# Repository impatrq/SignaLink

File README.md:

<div align="center">

</div>

<div align="center">

# Tus gestos hablan, SignaLink traduce

</div>

<table align="center">
<tr>
<td align="center">

</td>
<td align="center">

</td>
</tr>
</table>

## 📽️ Video de Presentación:

<a href="https://www.youtube.com/watch?v=zcVjxcC5Wm8&t=133s">Video de Presentación</a>

## 🔗 Acceso a página web:

<a href="https://signalink2025.com">Web Page</a>

## 🗓️ Objetivo de Proyecto:

SignaLink tiene como objetivo principal traducir la lengua de señas para lograr la inclusión de personas sordas en el ámbito escolar.

## 🌎 Visión a futuro

Otro objetivo propuesto a largo plazo es seguir difundiendo esta idea en futuras generaciones para poder proveerles un mejor manejo en la vida cotidiana a este tipo de personas, permitiendole agilizar su vida social o simplemente la comunicación sin barerras con otras personas.

## 💭 ¿De dónde surgió la idea?

Esta idea surgió en una conversación con la bibliotecaria de nuestra escuela que nos dio a conocer cuan reservadas son estas personas en la sociedad y cuantos desafios deben afrontar a diario. A traves de todo esto planteamos posibles soluciones para facilitarle sus vidas inicialmente en las escuelas y asi empezo toda esta aventura.

## 🖐 Descripción del proyecto:

Nuestro proyecto esta principalmente equipado con sensores flex, giroscopos y acelerómetros que detectan los movimientos de los dedos.

Estos datos que arrojan los sensores son capturados por un ESP32 C3 Super Mini ubicado en la muñeca y enviados a un Computer module 4 (CM4) a traves de un sistema de mensajeria (MQTT) ubicado en el pecho/cintura. Esta CM4 integra una Inteligencia Artificial (IA) que se encarga de procesar estos datos recibidos para descubrir que gesto se intentó hacer. Una vez realizado este proceso se convertira mediante PIPER-TTS a formato audio reproducible por un parlante, permitiendo así que las personas que se comunican mediante la lengua de señas puedan expresar su mensaje de forma audible para que cualquier receptor lo comprenda.

En paralelo, un micrófono direccional se encargará de captar la voz de la persona que quiera comunicarse, esas palabras serán procesadas por la CM4 utilizando un modelo de reconocimiento de voz (Vosk -> Offline) y en forma de texto se mostrará finalmente a través de un LCD OLED (SSD1306)

<div align="center">

</div>

## 🛠️ Componentes a utilizar:

| Componentes                     | Links                                                                                                                                                                                                                                                                                                                                                                                                                                                                                                                                                                                                                                                                                                                                                                                            |
| ------------------------------- | ------------------------------------------------------------------------------------------------------------------------------------------------------------------------------------------------------------------------------------------------------------------------------------------------------------------------------------------------------------------------------------------------------------------------------------------------------------------------------------------------------------------------------------------------------------------------------------------------------------------------------------------------------------------------------------------------------------------------------------------------------------------------------------------------ |
| Raspberry Pi Compute Module 4   | [Raspberry Pi Compute Module 4 - ELEMON](https://www.elemon.com.ar/products/detail/code/AR681RA642)                                                                                                                                                                                                                                                                                                                                                                                                                                                                                                                                                                                                                                                                                              |
| ESP32-C3 Super Mini             | [ESP32-C3 Super Mini - Mercado Libre](https://articulo.mercadolibre.com.ar/MLA-1933180704-placa-desarrollo-esp32-c3-super-mini-wifi-bluetooth-sgk-_JM#polycard_client=search-nordic&position=18&search_layout=grid&type=item&tracking_id=a6179d80-9c2f-448f-931d-3f6b0744610e&wid=MLA1933180704&sid=search)                                                                                                                                                                                                                                                                                                                                                                                                                                                                                      |
| Sensores Flex                   | [Sensores Flex - Mercado Libre](https://articulo.mercadolibre.com.ar/MLA-621168012-flex-sensor-45-o-degrees-10-30-kohms-sensor-reflectivo-_JM#polycard_client=search-nordic&position=22&search_layout=stack&type=item&tracking_id=d09a116e-7fa9-4e61-b811-829b67d77fb1&wid=MLA621168012&sid=search)                                                                                                                                                                                                                                                                                                                                                                                                                                                                                              |
| Parlante                        | [ Mini Parlante- Mercado Libre](https://articulo.mercadolibre.com.ar/MLA-926965993-mini-parlante-mylar-50mm-8-ohms-05w-audio-arduino-nubbeo-_JM#polycard_client=search-nordic&position=8&search_layout=stack&type=item&tracking_id=5afdc171-789b-4858-9908-6e8644b818c2&wid=MLA926965993&sid=search)                                                                                                                                                                                                                                                                                                                                                                                                                                                                                             |
| Modulo Amplificador             | [ PAM8403 - Mercado Libre](https://www.mercadolibre.com.ar/mini-amplificador-digital-pam8403-audio-estereo-3w-nubbeo/up/MLAU237136317?pdp_filters=item_id:MLA872767061&matt_tool=93069454&matt_internal_campaign_id=345755545&matt_word=&matt_source=google&matt_campaign_id=22943760643&matt_ad_group_id=187007705242&matt_match_type=&matt_network=g&matt_device=c&matt_creative=774178775740&matt_keyword=&matt_ad_position=&matt_ad_type=pla&matt_merchant_id=5381779497&matt_product_id=MLA872767061&matt_product_partition_id=2424609165763&matt_target_id=pla-2424609165763&cq_src=google_ads&cq_cmp=22943760643&cq_net=g&cq_plt=gp&cq_med=pla&gad_source=1&gad_campaignid=22943760643&gclid=CjwKCAjwx-zHBhBhEiwA7Kjq67psJOORAgfFyvkqrNDuf2QOjtHhOilyAz1d6FZmyiqMh8wAA7Ma8xoCBCEQAvD_BwE) |
| Micrófono                       | [ Corbatero Carello C11 - Mercado Libre](https://www.mercadolibre.com.ar/microfono-inalambrico-corbatero-lavalier-carrello-c11-adaptador-usb-c-a-lightning-estuche-de-carga-antena-usb-c-1x-microfono-color-negro/p/MLA44118282)                                                                                                                                                                                                                                                                                                                                                                                                                                                                                                                                                                 |
| Baterias                        | [ Lipo 3.7V - Mercado Libre](https://articulo.mercadolibre.com.ar/MLA-823943306-bateria-litio-polimero-lipo-37v-1200mah-drones-helicopteros-_JM#polycard_client=search-nordic&position=11&search_layout=stack&type=item&tracking_id=00997a8f-a302-41cd-929e-7f9b96588b73&wid=MLA823943306&sid=search)                                                                                                                                                                                                                                                                                                                                                                                                                                                                                            |
| Sensor Giroscopo y Acelerometro | [MPU6050 - Mercado Libre](https://articulo.mercadolibre.com.ar/MLA-1464073846-acelerometro-giroscopo-mpu6050-6-ejes-gy-521-pic-arduino-_JM#polycard_client=search-nordic&position=4&search_layout=grid&type=item&tracking_id=1592b6fb-67c2-4128-a466-704776d0e915&wid=MLA1464073846&sid=search)                                                                                                                                                                                                                                                                                                                                                                                                                                                                                                  |
| Step Up 5V                      | [ MT3608 - Mercado Libre](https://articulo.mercadolibre.com.ar/MLA-1410408453-5-fuente-mt3608-step-up-buck-boost-elevador-dc-dc-28v-2a-_JM#polycard_client=search-nordic&backend_model=search-backend&position=20&search_layout=stack&type=item&tracking_id=d4915a5c-d355-42a4-b246-3798a3844913&wid=MLA1410408453&sid=search)                                                                                                                                                                                                                                                                                                                                                                                                                                                                   |
| LCD OLED                        | [LCD SSD1306 - Mercado Libre](https://articulo.mercadolibre.com.ar/MLA-1899526208-pantalla-display-oled-091-pulgadas-128x32-i2c-ssd1306-_JM)                                                                                                                                                                                                                                                                                                                                                                                                                                                                                                                                                                                                                                                     |

## 💻 Instalación y Uso

1. Clonar el repositorio:
   ```bash
   git clone https://github.com/impatrq/SignaLink
   ```
2. Entrar a la carpeta rpizero2W.
   ```bash
   cd SignaLink/rpizero2W
   ```
3. Darle permisos de ejecucion al script de instalación.
   ```bash
   chmod +x install.sh
   ```
4. Ejecutar el Script.
   ```bash
   ./install.sh
   ```
5. Comenzar su uso.

## 🧑🏽‍💻 Integrantes

| Integrantes           | Responsabilidades                     | Tareas Secundarias                 |
| --------------------- | ------------------------------------- | ---------------------------------- |
| Albornoz Thiago       | Gestión de Redes Sociales y Marketing | Desarrollo de Software             |
| Erbino Sebastián      | Diseño del Prototipo                  | Integración de hardware            |
| Franco Valentin       | Armado de Hardware                    | Instalación y conexión de hardware |
| Lesme Franco          | Armado de software                    | Diseño del prototipo               |
| Poggi Lorenzo         | Registro de Seguimiento               | Programación del sistema           |
| Sarniguette Valentino | Prueba electronica                    | Armado de circuitos                |

## 🤝 Colaboración:

Este es el comienzo de un prototipo realizado a base de nuestros conocimientos, si le gustaria formar parte de SignaLink, nos ayudaría su colaboración en:

- Perfeccionar el código.
- Mejorar la infraestructura tecnológica.
- Creación de manuales y realización de pruebas.
- Apoyo financiero para la investigación y el desarrollo.

## 📱 Contactanos:

## 📱 Contactos personales

| Integrante                | Gmail                                                                                                                                                                          | LinkedIn                                                                                                                                                                                                                                            |
| ------------------------- | ------------------------------------------------------------------------------------------------------------------------------------------------------------------------------ | --------------------------------------------------------------------------------------------------------------------------------------------------------------------------------------------------------------------------------------------------- |
| **Albornoz Thiago**       |  |                                                                         |
| **Erbino Sebastian**      |              |                                                          |
| **Franco Valentin**       |     |  |
| **Lesme Franco**          |       |                                                                                 |
| **Poggi Lorenzo**         |     |    |
| **Sarniguette Valentino** |   |                                                                          |

---

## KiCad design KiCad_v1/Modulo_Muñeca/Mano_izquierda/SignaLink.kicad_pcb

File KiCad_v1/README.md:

# Carpeta de Trabajo - Diseño de Placas 

Utilizamos **KiCad** para el diseño de circuitos impresos (PCB). Llevamos con esta aplicacion la creacion de dos PCBs:

## Módulo Muñeca

El diseño de la placa está optimizado en un formato compacto de 30 mm por 50 mm, lo que permite reducir al máximo su tamaño sin afectar el rendimiento. Su objetivo principal es garantizar un sensado preciso de los gestos de la mano, combinando comodidad de uso con eficiencia en la interpretación de movimientos. 

El módulo integra un ESP32-C3 Super Mini como microcontrolador central, acompañado por el chip MPU6050 para la detección de aceleración y giro, una pantalla OLED SSD1306 para la visualización de información en tiempo real, sensores flexibles que registran la flexión de los dedos y un módulo de carga USB que facilita la autonomía energética y la recarga de Batería Lipo. Gracias a esta integración, el sistema se presenta como una solución ligera, compacta y confiable para la captura e interpretación de gestos manuales.

<h3>Mano Izquierda</h3>

- Diseño 3D:
<div align="center">

</div>

- Esquemático
<div align="center">

</div>

- Diseño de placa sin plano de masa
<div align="center">

</div>

- Diseño de placa con plano de masa:
<div align="center">

</div>

<h3>Mano Derecha</h3>

- Diseño 3D:
<div align="center">

</div>

- Esquemático
<div align="center">

</div>

- Diseño de placa sin plano de masa
<div align="center">

</div>

- Diseño de placa con plano de masa:
<div align="center">

</div>

## Modulo Pecho: 

El módulo del pecho constituye el núcleo de procesamiento de SignaLink. En su diseño se integra una Raspberry Pi Compute Module 4 (RCM4), que actúa como el procesador principal encargado de coordinar y analizar la información proveniente de los demás periféricos. Esta capacidad de cómputo permite realizar el filtrado de datos en tiempo real y gestionar la comunicación con el resto del sistema a través del protocolo MQTT, asegurando una transmisión eficiente y confiable.

Además de la RCM4, la placa incorpora un DAC con amplificador PAM junto con los conectores para parlante, lo que posibilita la conversión de gestos a audio de manera clara y directa. Gracias a esta integración, el sistema no solo traduce los movimientos capturados en datos procesables, sino que también ofrece la salida de voz que convierte las señas en un medio de comunicación audible.

De esta forma, el módulo del pecho se consolida como el cerebro y la voz de SignaLink, combinando procesamiento, conectividad y salida de audio en una sola unidad compacta y eficiente.

- Diseño 3D:
<div align="center">

</div>

- Diseño 3D:
<div align="center">

</div>

- Esquemático
<div align="center">

</div>

- Diseño de placa sin plano de masa
<div align="center">

</div>

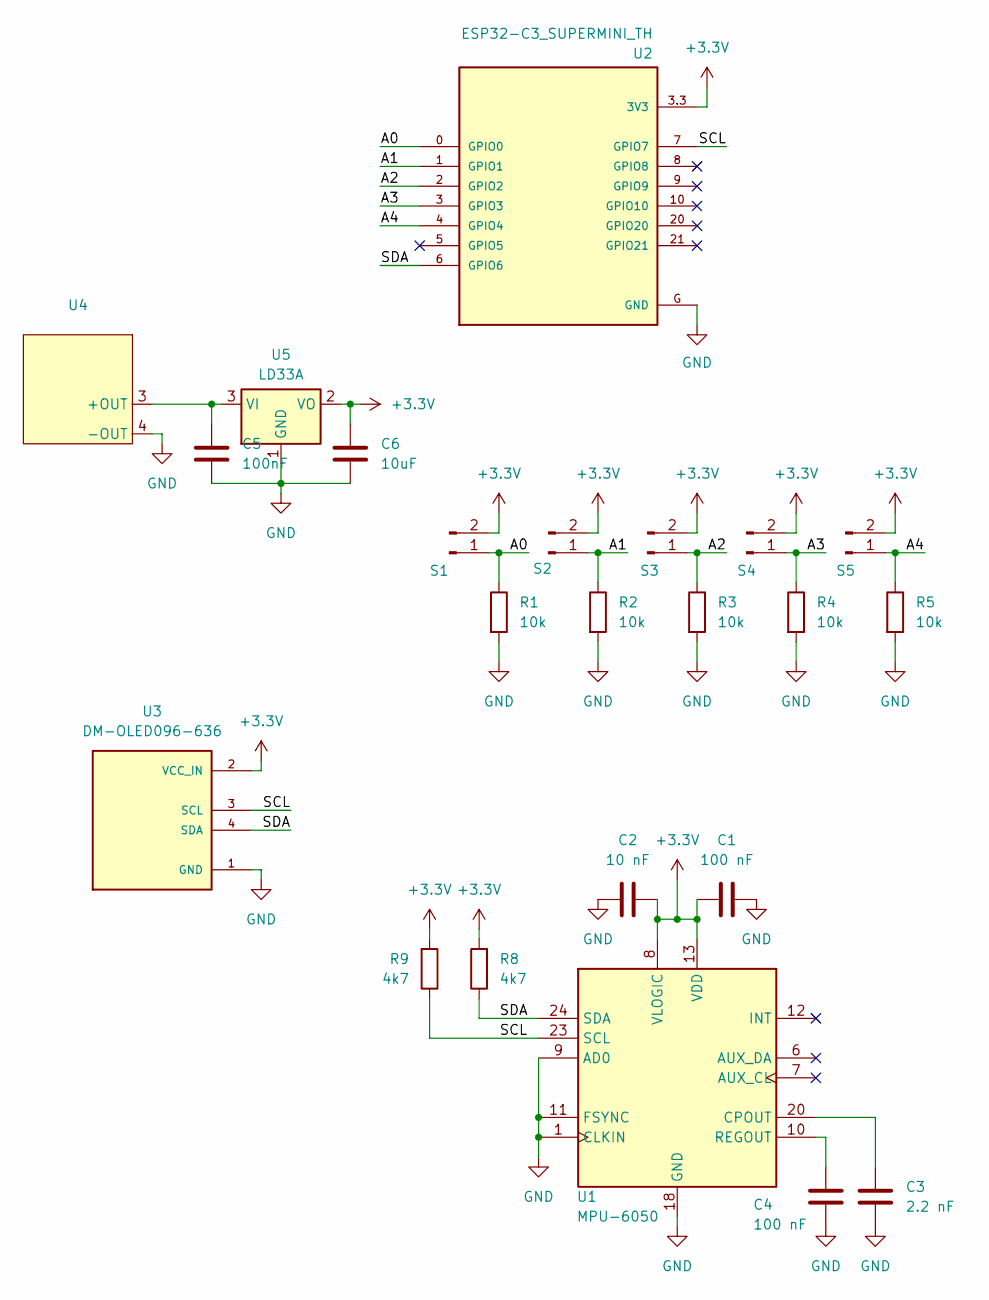
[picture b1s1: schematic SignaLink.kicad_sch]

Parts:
C1, C4: 100 nF; C_0805_2012Metric
C2: 10 nF; C_0805_2012Metric
C3: 2.2 nF; C_0805_2012Metric
C5: 100nF; C_0805_2012Metric
C6: 10uF; C_0805_2012Metric
R1, R2, R3, R4, R5: 10k; R_0805_2012Metric
R8, R9: 4k7; R_0805_2012Metric
S1: SF 1; PinHeader_1x02_P2.54mm_Vertical
S2: SF 2; PinHeader_1x02_P2.54mm_Vertical
S3: SF 3; PinHeader_1x02_P2.54mm_Vertical
S4: SF 4; PinHeader_1x02_P2.54mm_Vertical
S5: SF 5; PinHeader_1x02_P2.54mm_Vertical
U1: MPU-6050; InvenSense_QFN-24_4x4mm_P0.5mm
U2: ESP32-C3_SUPERMINI_TH; MODULE_ESP32-C3_SUPERMINI_TH
U3: DM-OLED096-636; PinHeader_1x04_P2.54mm_Vertical; PARTREV 2018-09-10
U4: TP4056_NEW
U5: LD33A; SOT-223-3_TabPin2

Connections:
+3.3V: C1.1, C2.2, C6.1, R8.2, R9.2, S1.2, S2.2, S3.2, S4.2, S5.2, U1.8 (VLOGIC), U1.13 (VDD), U2.3.3 (3V3), U3.2 (VCC_IN), U5.2 (VO)
/A0: R1.1, S1.1, U2.0 (GPIO0)
/A1: R2.1, S2.1, U2.1 (GPIO1)
/A2: R3.1, S3.1, U2.2 (GPIO2)
/A3: R4.1, S4.1, U2.3 (GPIO3)
/A4: R5.1, S5.1, U2.4 (GPIO4)
/SCL: R9.1, U1.23 (SCL), U2.7 (GPIO7), U3.3 (SCL)
/SDA: R8.1, U1.24 (SDA), U2.6 (GPIO6), U3.4 (SDA)
GND: C1.2, C2.1, C3.2, C4.2, C5.2, C6.2, R1.2, R2.2, R3.2, R4.2, R5.2, U1.1 (CLKIN), U1.9 (AD0), U1.11 (FSYNC), U1.18 (GND), U2.G (GND), U3.1 (GND), U4.4 (-OUT), U5.1 (GND)
unnamed: C3.1, U1.20 (CPOUT)
unnamed: C4.1, U1.10 (REGOUT)
unnamed: C5.1, U4.3 (+OUT), U5.3 (VI)

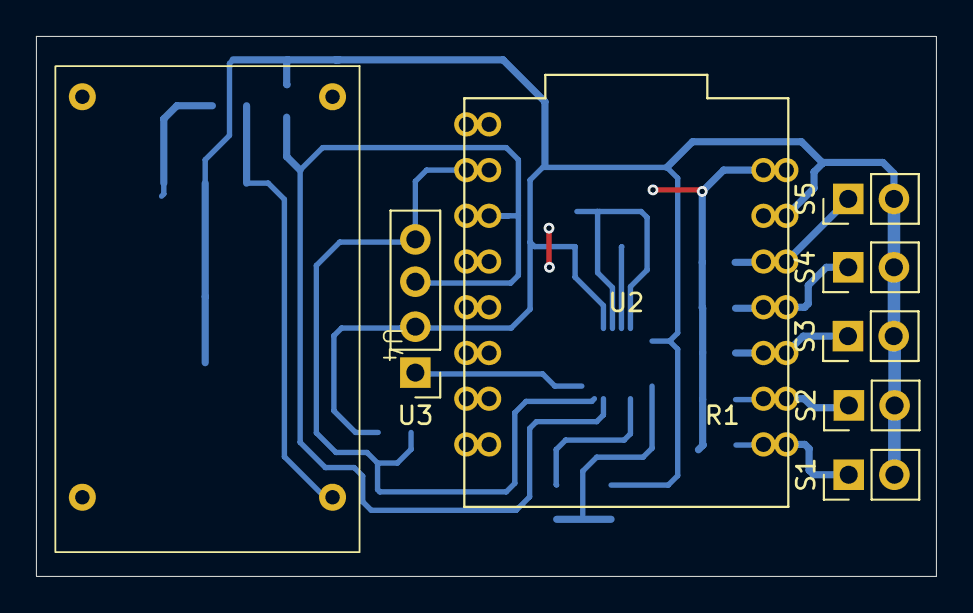
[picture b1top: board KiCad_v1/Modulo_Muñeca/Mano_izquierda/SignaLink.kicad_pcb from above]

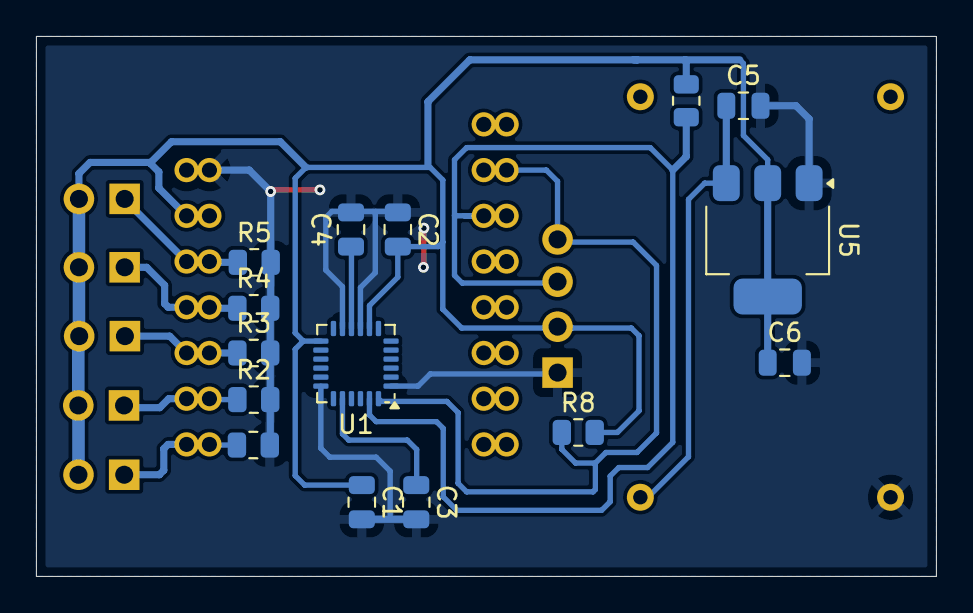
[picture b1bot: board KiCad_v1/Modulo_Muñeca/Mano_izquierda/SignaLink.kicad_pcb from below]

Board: 2 copper layers, 50.0 x 30.0 mm, 23 parts (15 on the bottom side), 12 nets.

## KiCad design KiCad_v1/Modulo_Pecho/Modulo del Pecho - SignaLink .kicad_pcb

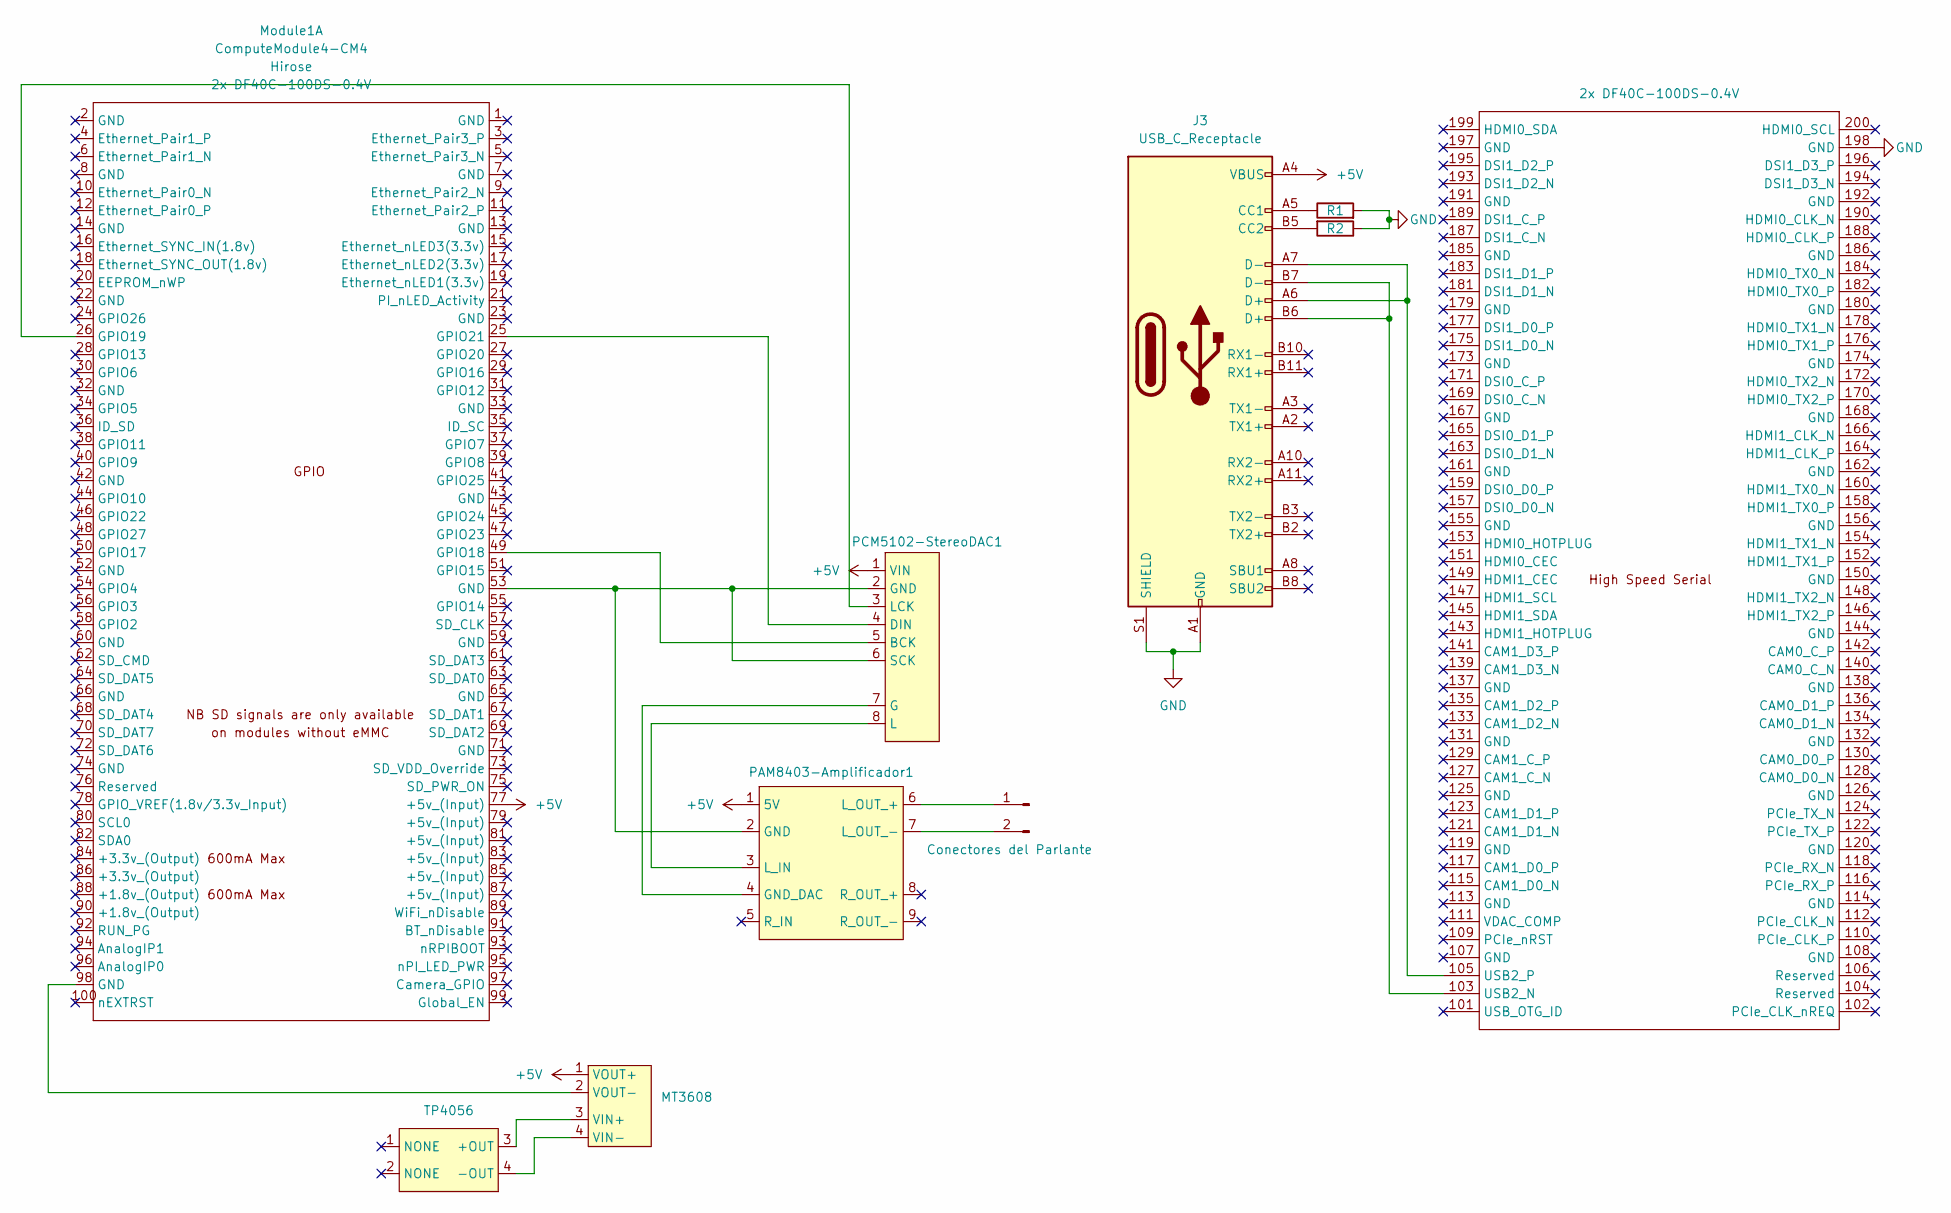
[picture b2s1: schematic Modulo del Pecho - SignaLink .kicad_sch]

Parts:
J1: Conectores del Parlante
J3: USB_C_Receptacle; USB_C_Receptacle_G-Switch_GT-USB-7010ASV
MT3608: MT3608
Module1: ComputeModule4-CM4; Raspberry-Pi-4-Compute-Module
PAM8403-Amplificador1: PAM8403
PCM5102-StereoDAC1: PCM5102
R1, R2: 5k1; R_0805_2012Metric
UTP4056: TP4056

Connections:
+5V: J3.A4 (VBUS), J3.A9 (VBUS), J3.B4 (VBUS), J3.B9 (VBUS), MT3608.1 (VOUT+), Module1.77 (+5v_(Input)), PAM8403-Amplificador1.1 (5V), PCM5102-StereoDAC1.1 (VIN)
GND: J3.A1 (GND), J3.A12 (GND), J3.B1 (GND), J3.B12 (GND), J3.S1 (SHIELD), Module1.198 (GND), R1.2, R2.1
unnamed: J1.2 (Pin_1), PAM8403-Amplificador1.7 (L_OUT_-)
unnamed: J1.1 (Pin_2), PAM8403-Amplificador1.6 (L_OUT_+)
unnamed: J3.A5 (CC1), R1.1
unnamed: J3.B5 (CC2), R2.2
unnamed: MT3608.3 (VIN+), UTP4056.3 (+OUT)
unnamed: MT3608.4 (VIN-), UTP4056.4 (-OUT)
unnamed: MT3608.2 (VOUT-), Module1.98 (GND)
unnamed: Module1.49 (GPIO18), PCM5102-StereoDAC1.5 (BCK)
unnamed: Module1.26 (GPIO19), PCM5102-StereoDAC1.3 (LCK)
unnamed: Module1.25 (GPIO21), PCM5102-StereoDAC1.4 (DIN)
unnamed: J3.B6 (D+), J3.B7 (D-), Module1.103 (USB2_N)
unnamed: J3.A6 (D+), J3.A7 (D-), Module1.105 (USB2_P)
unnamed: Module1.53 (GND), PAM8403-Amplificador1.2 (GND), PCM5102-StereoDAC1.2 (GND), PCM5102-StereoDAC1.6 (SCK)
unnamed: PAM8403-Amplificador1.4 (GND_DAC), PCM5102-StereoDAC1.7 (G)
unnamed: PAM8403-Amplificador1.3 (L_IN), PCM5102-StereoDAC1.8 (L)

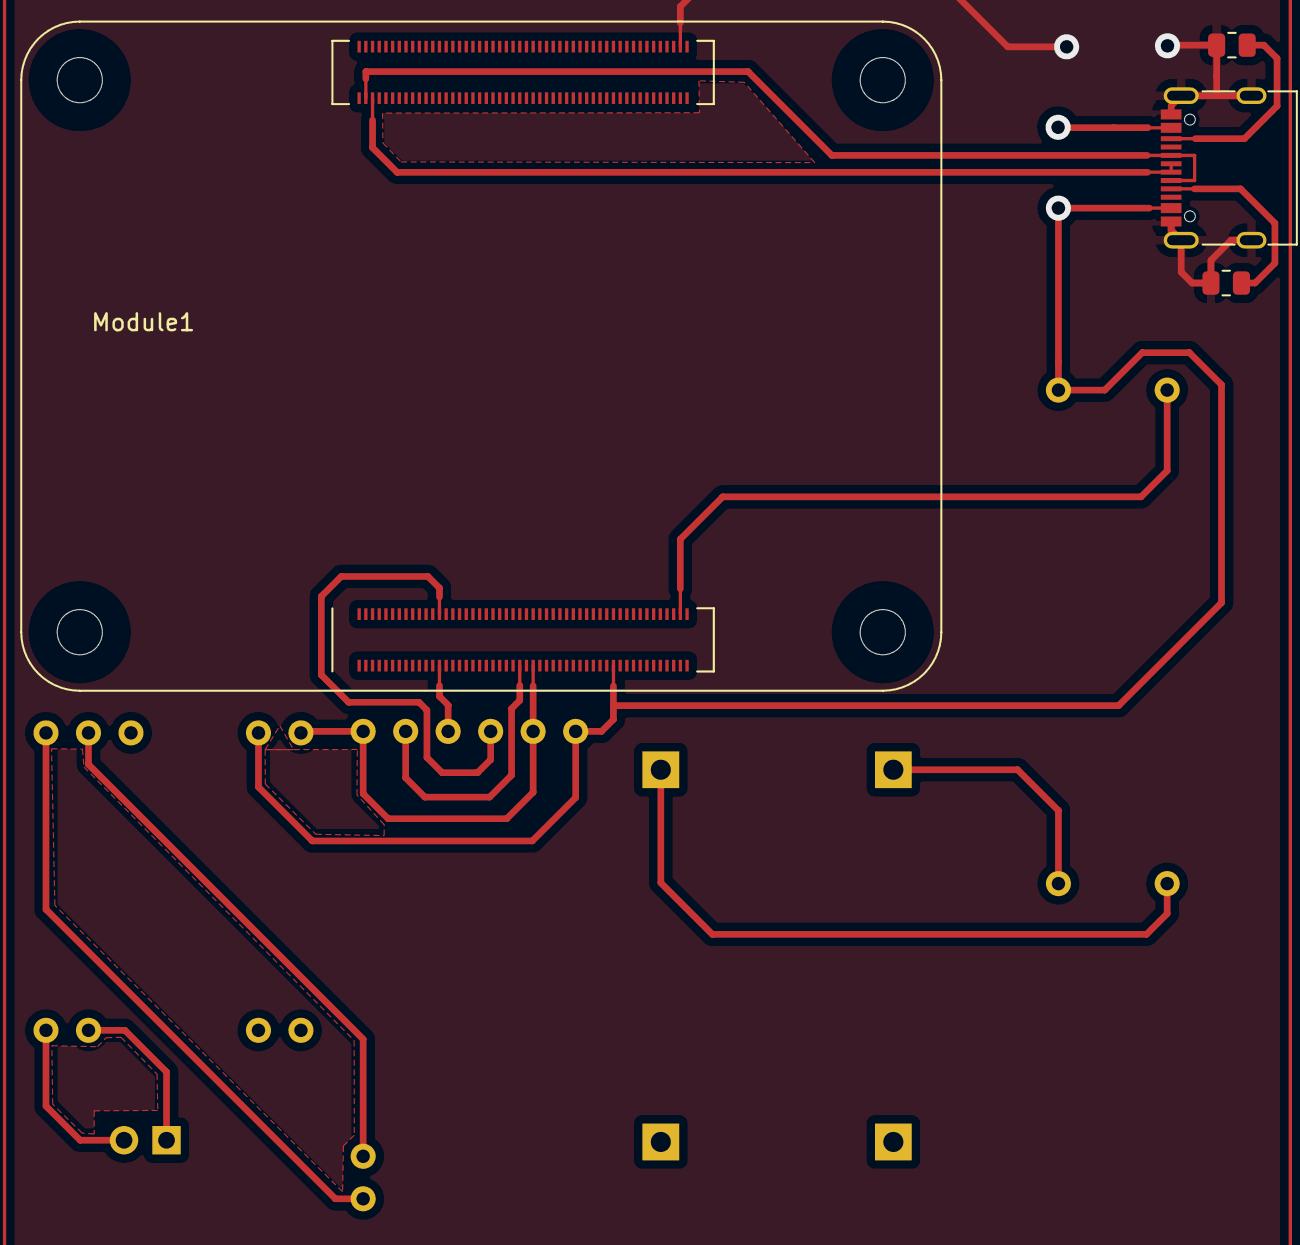
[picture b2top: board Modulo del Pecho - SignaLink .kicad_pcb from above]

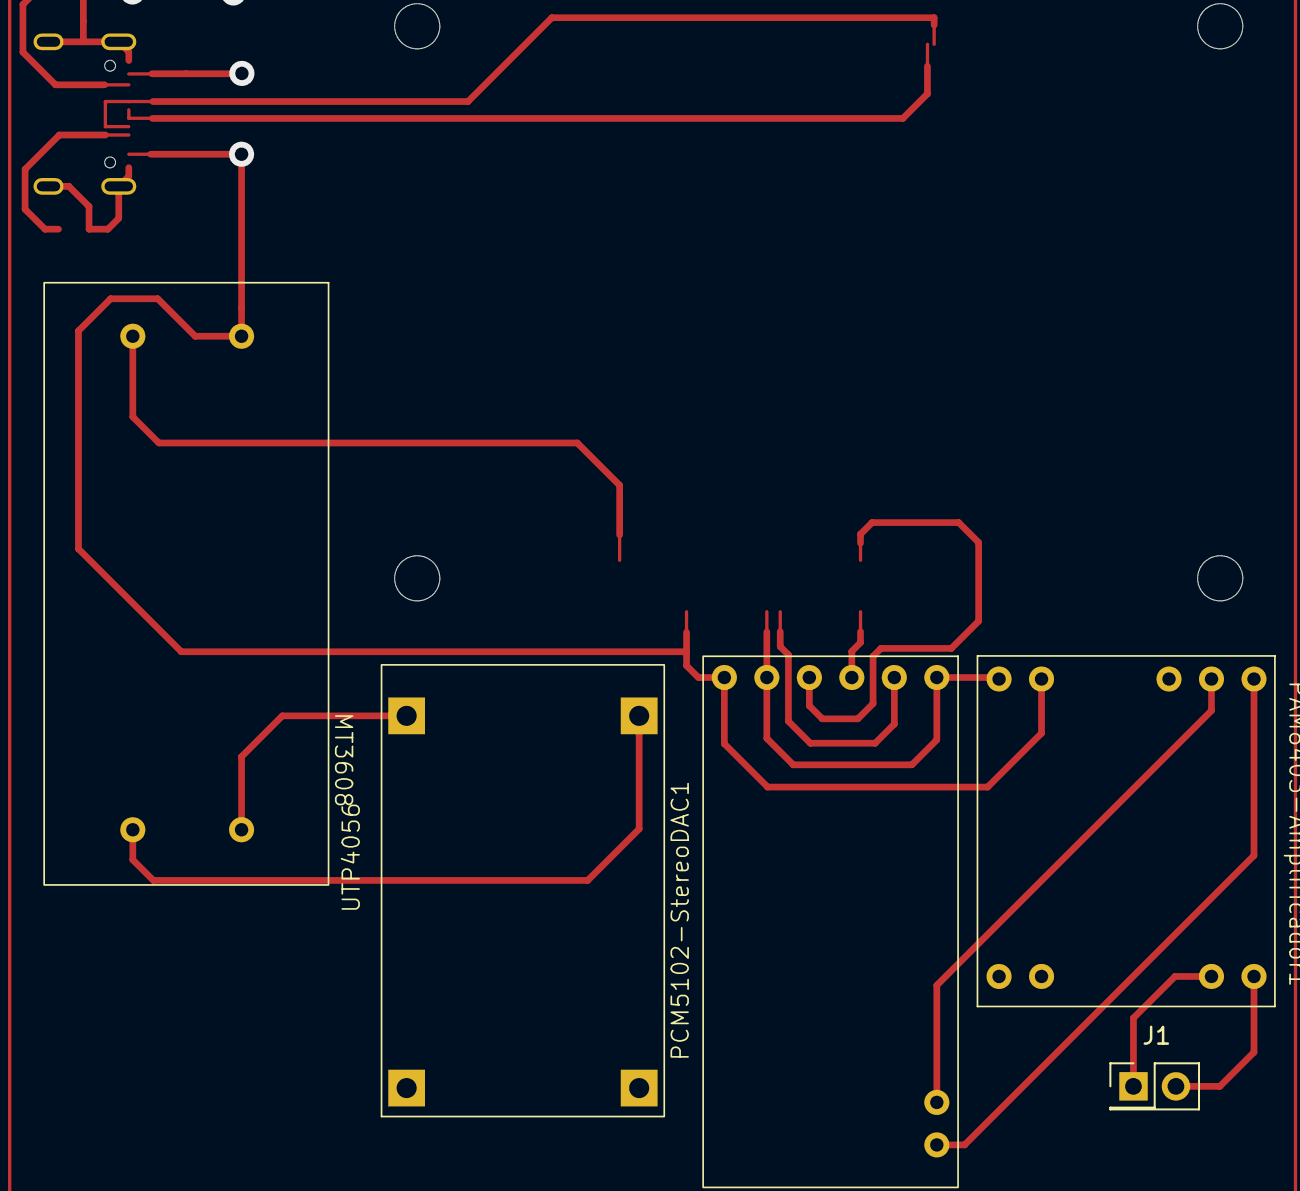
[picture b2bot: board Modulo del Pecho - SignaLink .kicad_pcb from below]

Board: 2 copper layers, 9 parts (5 on the bottom side), 17 nets.

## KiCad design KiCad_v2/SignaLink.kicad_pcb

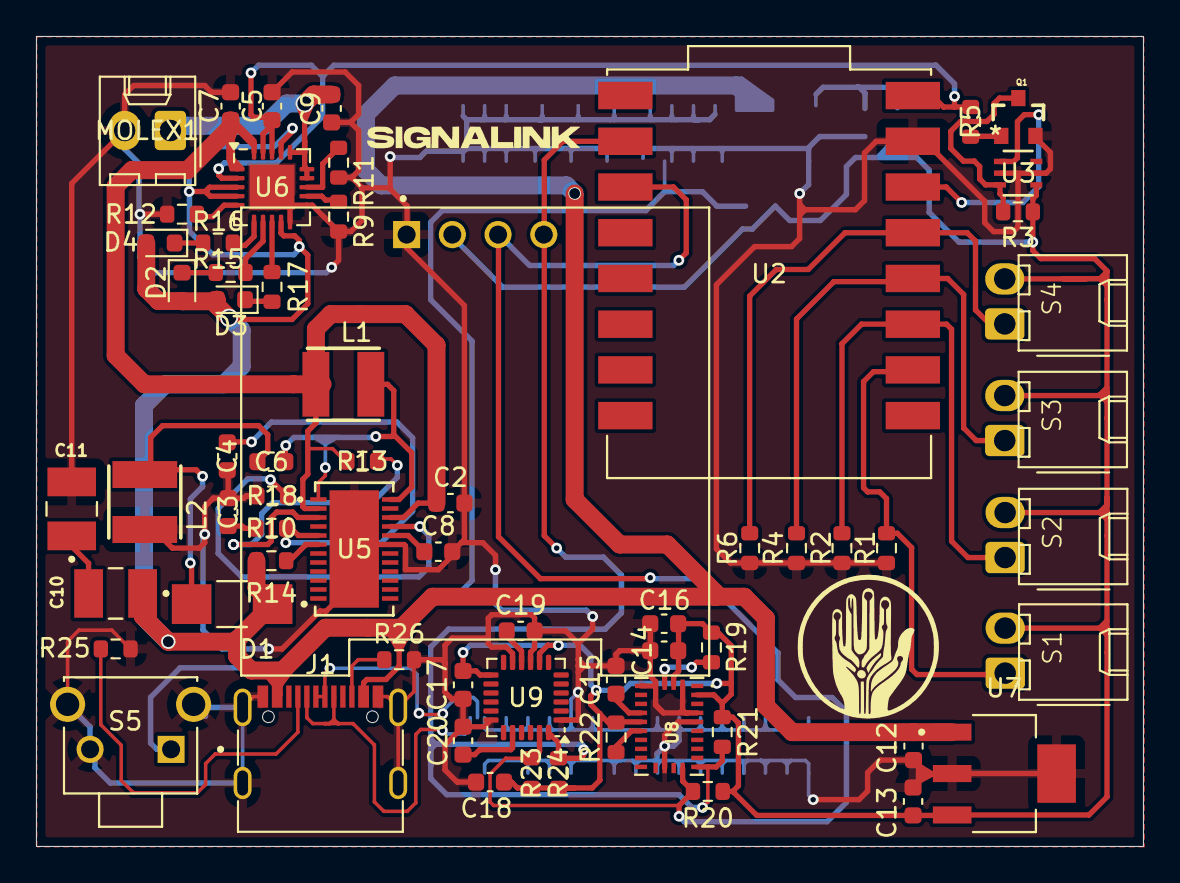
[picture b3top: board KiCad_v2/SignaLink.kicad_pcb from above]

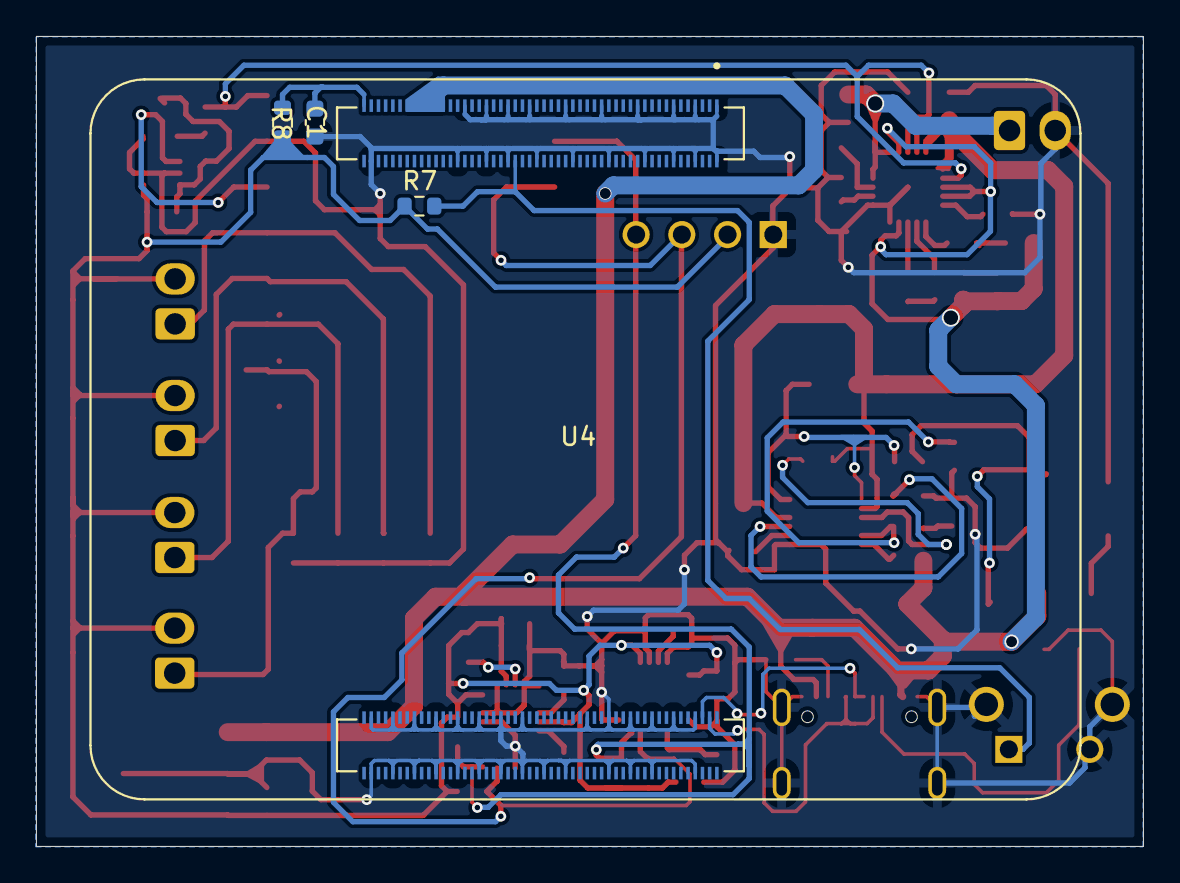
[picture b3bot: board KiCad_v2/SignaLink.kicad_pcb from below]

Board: 2 copper layers, 61.5 x 45.0 mm, 69 parts (4 on the bottom side), 44 nets.

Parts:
C1: 100nf; C_0603_1608Metric
C2: 22uF; C_0603_1608Metric
C3: 1.5nF; C_0603_1608Metric
C4: 47pF; C_0603_1608Metric
C5, C6, C16: 10uF; C_0603_1608Metric
C7, C9: 4.7uF; C_0603_1608Metric
C8, C14, C15: 0.1uF; C_0603_1608Metric
C10, C11: 68uF; CAP_6TPB68M
C12: 0.47uF; C_0603_1608Metric
C13: 33uF; C_0603_1608Metric
C17: 10 nF; C_0603_1608Metric
C18, C19: 100 nF; C_0603_1608Metric
C20: 2.2 nF; C_0603_1608Metric
D1: SS34
D2, D3, D4: LED; LED_0603_1608Metric
J1: USB_C_Receptacle; USB_C_Receptacle_G-Switch_GT-USB-7010ASV
L1, L2: 2.7uH; COILSR
MOLEX1: SF 1; Molex_KK-254_AE-6410-02A_1x02_P2.54mm_Vertical
Q1: MMBT3904
R1, R2, R4, R6, R7, R8, R12, R19, R22: 10k; R_0603_1608Metric
R3, R13: 100k; R_0603_1608Metric
R5, R20, R21, R23, R24: 4k7; R_0603_1608Metric
R9: 22k; R_0603_1608Metric
R10: 14.7k; R_0603_1608Metric
R11: 1k; R_0603_1608Metric
R14: 45.3k; R_0603_1608Metric
R15, R16, R17: 470; R_0603_1608Metric
R18: 120k; R_0603_1608Metric
R25, R26: 5k1; R_0603_1608Metric
S1: SF 2; Molex_Signalink
S2: SF 3; Molex_Signalink
S3: SF 4; Molex_Signalink
S4: SF 5; Molex_Signalink
S5: PULSADOR
U1: DM-OLED096-636; MODULE_DM-OLED096-636
U2: ESP32-C3_SUPERMINI_TH; MODULE_ESP32-C3_SUPERMINI
U3: MIC94063YC6-TR; SC-70_C6_MCH-L
U4: CM4102008; MODULE_CM4102008
U5: LT8582EDKD-PBF; DKD_ADI-M
U6: MCP73871; QFN-20-1EP_4x4mm_P0.5mm_EP2.5x2.5mm
U7: LM3940IMP-3.3; SOT230P700X180-4N
U8: BNO085; IC_BNO085
U9: MPU-6050; InvenSense_QFN-24_4x4mm_P0.5mm

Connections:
+3.3V: C13.1, C14.2, C16.2, C17.2, C18.1, R3.1, R7.1, R8.1, R19.2, R20.2, R21.1, R22.2, R23.2, R24.2, S1.2, S2.2, S3.2, S4.2, U1.2 (VCC_IN), U3.4 (VIN), U7.3 (OUT), U8.3 (VDD), U8.10 (CLKSEL0), U8.28 (VDDIO), U9.8 (VLOGIC), U9.13 (VDD)
+5V: C10.1, C12.1, D1.C, D2.2 (A), D3.2 (A), D4.2 (A), J1.A4 (VBUS), J1.A9 (VBUS), J1.B4 (VBUS), J1.B9 (VBUS), R14.2, U4.77 (+5V(INPUT)), U4.79 (+5V(INPUT)), U4.81 (+5V(INPUT)), U4.83 (+5V(INPUT)), U4.85 (+5V(INPUT)), U4.87 (+5V(INPUT)), U6.3 (SEL), U6.4 (PROG2), U6.9 (~TE), U6.17 (CE), U7.1 (IN)
/A1: R1.1, S1.1, U2.1 (GPIO1)
/A2: R2.1, S2.1, U2.2 (GPIO2)
/A3: R4.1, S3.1, U2.3 (GPIO3)
/A4: R6.1, S4.1, U2.4 (GPIO4)
/MIC_OUT: U2.3.3 (3V3), U3.1 (VOUT)
/SCL: R20.1, R23.1, U1.3 (SCL), U2.7 (GPIO7), U8.19 (H_SCL/SCK/RX), U9.23 (SCL)
/SDA: R21.2, R24.1, U1.4 (SDA), U2.6 (GPIO6), U8.20 (H_SDA/H_MISO/TX), U9.24 (SDA)
/USB_N: J1.B6 (D+), J1.B7 (D-), U4.103 (USB_N)
/USB_P: J1.A6 (D+), J1.A7 (D-), U4.105 (USB_P)
/USB_PORT: C5.2, R5.1, U2.5V, U6.2 (VPCC), U6.18 (IN), U6.19 (IN)
/power_supply/OUT_MCP: C2.1, C7.1, L1.1, R13.1, U5.2 (VIN1), U5.22 (*SHDN1), U6.1 (OUT), U6.20 (OUT)
GND: C1.2, C2.2, C3.2, C4.2, C5.1, C7.2, C8.2, C9.2, C11.2, C12.2, C13.2, C14.1, C15.2, C16.1, C17.1, C18.2, C19.2, C20.2, J1.A1 (GND), J1.A12 (GND), J1.B1 (GND), J1.B12 (GND), J1.S1 (SHIELD), L2.2, MOLEX1.2, Q1.2, R1.2, R2.2, R4.2, R6.2, R9.1, R11.2, R12.1, R18.2, R25.2, R26.2, S5.2, S5.3 (GND), S5.4 (GND), U1.1 (GND), U2.G (GND), U3.2 (GND), U3.5 (GND), U4.1 (GND), U4.2 (GND), U4.7 (GND), U4.8 (GND), U4.13 (GND), U4.14 (GND), U4.22 (GND), U4.23 (GND), U4.32 (GND), U4.33 (GND), U4.42 (GND), U4.43 (GND), U4.52 (GND), U4.53 (GND), U4.59 (GND), U4.60 (GND), U4.65 (GND), U4.66 (GND), U4.71 (GND), U4.74 (GND), U4.98 (GND), U4.107 (GND), U4.108 (GND), U4.113 (GND), U4.114 (GND), U4.119 (GND), U4.120 (GND), U4.125 (GND), U4.126 (GND), U4.131 (GND), U4.132 (GND), U4.137 (GND), U4.138 (GND), U4.144 (GND), U4.150 (GND), U4.155 (GND), U4.156 (GND), U4.161 (GND), U4.162 (GND), U4.167 (GND), U4.168 (GND), U4.173 (GND), U4.174 (GND), U4.179 (GND), U4.180 (GND), U4.185 (GND), U4.186 (GND), U4.191 (GND), U4.192 (GND), U4.197 (GND), U4.198 (GND), U5.19 (SYNC1), U5.25 (GND), U6.10 (V_{SS}), U6.11 (V_{SS}), U6.21 (V_{SS}), U7.2 (GND), U7.4 (GND), U8.2 (GND), U8.5 (PS1), U8.6 (PS0/WAKE), U8.17 (SA0/H_MOSI), U8.25 (GNDIO), U8.26 (XOUT32/CLKSEL1), U9.1 (CLKIN), U9.9 (AD0), U9.11 (FSYNC), U9.18 (GND)
unnamed: C3.1, R10.2
unnamed: C6.2, D1.A, L2.1
unnamed: C10.2, C11.1
unnamed: D2.1 (K), R15.1
unnamed: D3.1 (K), R17.1
unnamed: D4.1 (K), R16.2
unnamed: J1.A5 (CC1), R25.1
unnamed: J1.B5 (CC2), R26.1
unnamed: C9.1, MOLEX1.1, U6.14 (V_{BAT}), U6.15 (V_{BAT}), U6.16 (V_{BAT_SENSE})
unnamed: Q1.1, R5.2
unnamed: Q1.3, R3.2, U3.3 (EN)
unnamed: C1.1, R8.2, U4.99 (GLOBAL_EN)
unnamed: R7.2, S5.1, U4.58 (GPIO2)
unnamed: R14.1, U5.6 (FBX1)
unnamed: R13.2, U5.3 (PG1)
unnamed: R18.1, U5.21 (RT1)
unnamed: C8.1, U5.20 (SS1)
unnamed: C6.1, L1.2, U5.1 (SWA1), U5.24 (SWB1)
unnamed: C4.1, R10.1, U5.5 (VC1)
unnamed: R11.1, U6.13 (PROG1)
unnamed: R9.2, U6.12 (PROG3)
unnamed: R17.2, U6.8 (STAT1/~LBO)
unnamed: R15.2, U6.7 (STAT2)
unnamed: R12.2, U6.5 (THERM)
unnamed: R16.1, U6.6 (~PG)
unnamed: C15.1, U8.9 (CAP)
unnamed: R19.1, U8.4 (~BOOT)
unnamed: R22.1, U8.11 (~RST)
unnamed: C20.1, U9.20 (CPOUT)
unnamed: C19.1, U9.10 (REGOUT)

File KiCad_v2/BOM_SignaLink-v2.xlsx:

Comment | Designator | Footprint | JLCPCB Part
22uF | C2 | C0603 | C86295
1.5nF | C3 | C0402 | C107022
47pF | C4 | C0603 | C94904
10uF | C5,C6 | C0603 | C19702
4.7uF | C7,C9 | C0603 | C1705
100nF | C8 | C0603 | C14663
68uF | C10,C11 | CAP_6TPB68M | C278372
470nF | C12 | C0603 | C513577
33uF | C13 | C0805 | C342635
SS34 | D1 | SMA_L4.3-W2.5-LS5.0-RD | C20622488
YLED0603B | D2,D3 | LED0603-FD | C19171394
YLED0603G | D4 | LED0603-FD | C19273151
2.2uH | L1,L2 | IND-SMD_L4.0-W4.0_SNR4018 | C913207
ZX-XH2.54-2PZZ | MOLEX1 | CONN-TH_2P-P2.50_HX25003-2A | C7429632
22K | R9 | R0603 | C31850
14.7K | R10 | R0603 | C2933148
1K | R11 | R0402 | C11702
10K | R12 | R0603 | C25804
100K | R13 | R0603 | C25803
45.3K | R14 | R0402 | C2933099
470.0 | R15,R16,R17 | R0603 | C23179
120K | R18 | R0603 | C25808
LT8582EDKD#PBF | U5 | DFN-24_L7.0-W4.0-P0.50-BL-EP | C107994
MCP73871-4CAI/ML | U6 | QFN-20_L4.0-W4.0-P0.50-TL-EP2.7 | C637761
LM3940IMP-3.3/NOPB | U7 | SOT-223_L6.5-W3.5-P2.30-LS7.0-BR | C140319
100nF | C1 | C0603 | C14663
GT-USB-7010ASV | J1 | USB-C-SMD_G-SWITCH_GT-USB-7010ASV | C2988369
MMBT3904 | Q1 | SOT-23-3_L2.9-W1.3-P1.90-LS2.4-BR | C51625775
10K | R1,R2,R4,R6,R7,R8 | R0603 | C25804
100K | R3 | R0603 | C25803
4.7K | R5 | R0402 | C25900
5.1K | R25,R26 | R0603 | C2907044
XY-XHB2.54-2A21 | S1,S2,S3,S4 | HDR-TH_2P-P2.50-H-F-W7.3-N | C19271395
TS80220-413-07528 | S5 | SW-TH_TS80220-413-07528 | C42400924
DM-OLED096-636_DM-OLED096-636 | U1 | MODULE_DM-OLED096-636
ESP32-C3_SUPERMINI_TH_ESP32-C3_SUPERMINI_TH | U2 | MODULE_ESP32-C3_SUPERMINI
MIC94063YC6-TR | U3 | SC-70-6_L2.0-W1.3-P0.65-LS2.1-BL | C515518
DF40C-100DS-0.4V(51) | U4-2 | CONN-SMD_DF40C-100DS-0.4V-51 | C597931
DF40C-100DS-0.4V(51) | U4-1 | CONN-SMD_DF40C-100DS-0.4V-51 | C597931
100nF | C14,C15,C18,C19 | C0603 | C14663
4.7K | C16,R20,R21,R23,R24 | R0603 | C23162
10nF | C17 | C0603 | C1589
2.2nF | C20 | C0402 | C1531
10K | R19 | R0603 | C25804
100K | R22 | R0603 | C25803
BNO085 | U8 | LGA-28_L5.2-W3.8-P0.50-BL | C5189642
MPU-6050 | U9 | QFN-24_L4.0-W4.0-P0.50-BL-EP2.7 | C24112

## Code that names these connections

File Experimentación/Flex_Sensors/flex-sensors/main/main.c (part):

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#include "esp_adc/adc_cali_scheme.h"

// Configuración
#define ADC_CHANNEL_0   ADC_CHANNEL_0 // GPIO0
#define ADC_CHANNEL_1   ADC_CHANNEL_1 // GPIO1
#define ADC_CHANNEL_2   ADC_CHANNEL_2 // GPIO2
#define ADC_CHANNEL_3   ADC_CHANNEL_3 // GPIO3
#define ADC_CHANNEL_4   ADC_CHANNEL_4 // GPIO4
#define ADC_UNIT        ADC_UNIT_1    // ADC1
#define R_FIXED         10000.0       // Ohmios (resistencia fija)
#define VCC             3.3           // Voltaje de referencia (3.3V)
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

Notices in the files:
README.md:
License: MIT
